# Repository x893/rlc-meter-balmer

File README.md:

# RLC-Meter-balmer
Complex impedance meter capable of measuring impedance in the range 1 mOhm - 10 MW at a frequency of 100 Hz to 250 kHz. Much attention is paid to measurement accuracy. Accuracy of better than 0.5% in the range 10 ohms - 100 ohms at frequencies of 100 Hz - 100 kHz.

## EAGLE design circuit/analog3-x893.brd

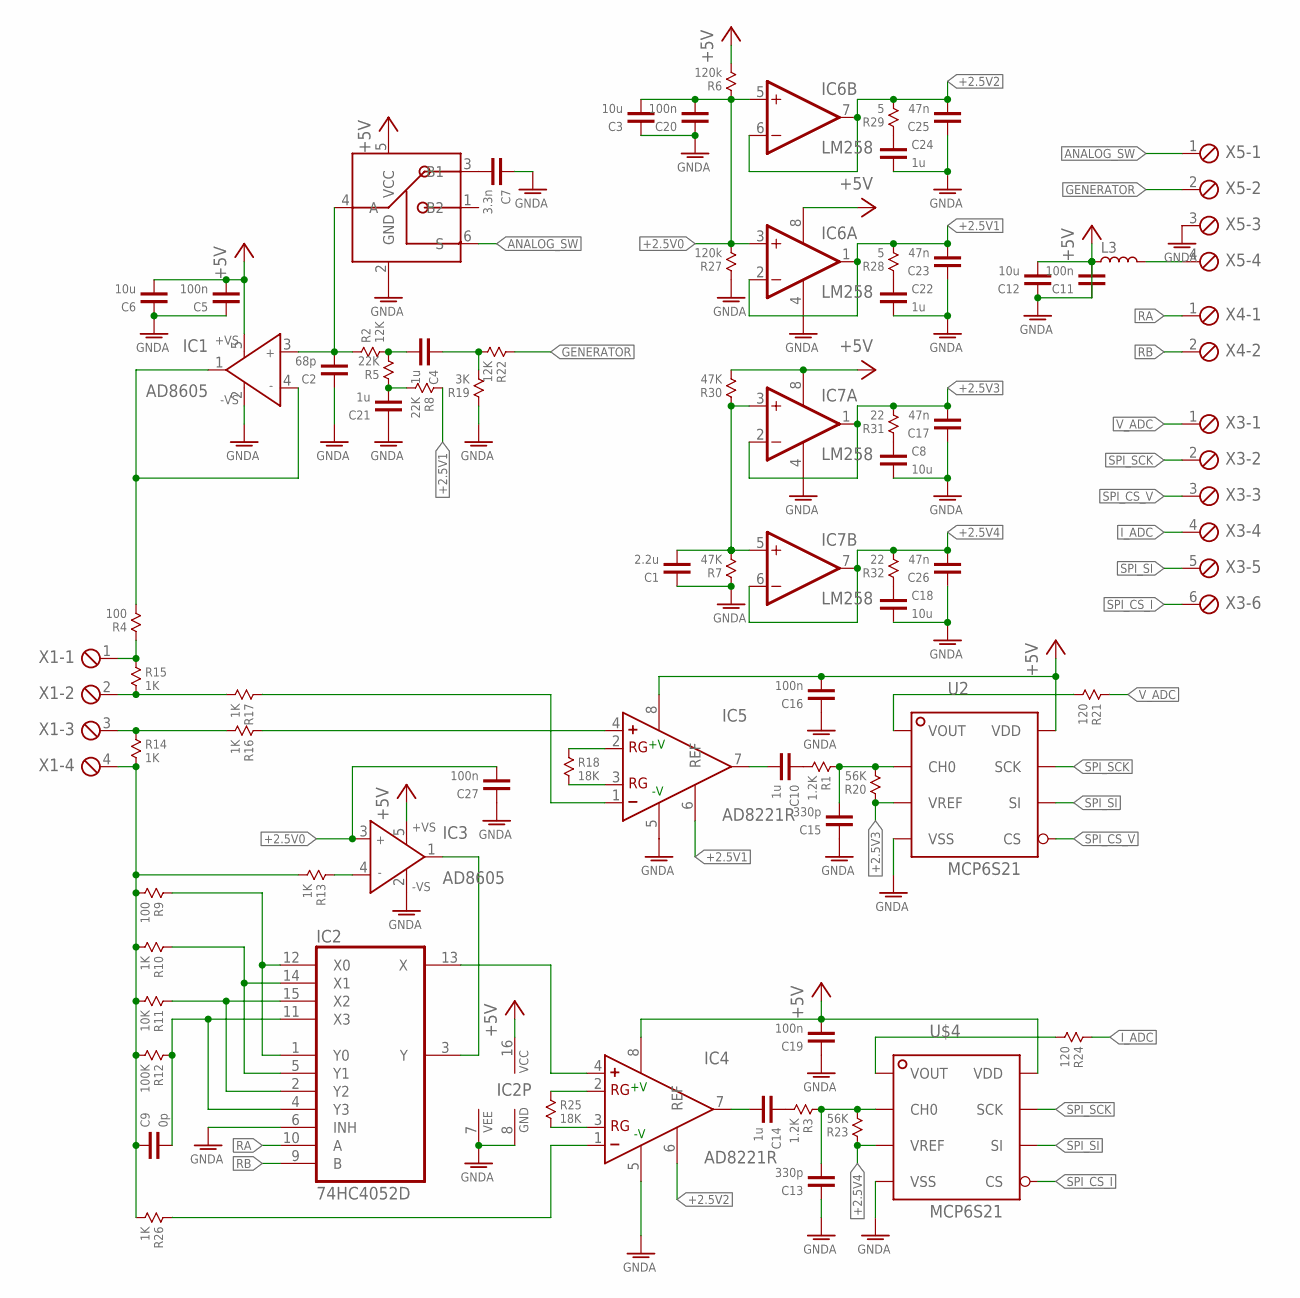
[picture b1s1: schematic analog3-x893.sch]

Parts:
C1: 2.2u; 0603
C2: 68p; 0603
C3, C6, C8, C12, C18: 10u; 0603
C4, C10, C14, C21, C22, C24: 1u; 0603
C5, C11, C16, C19, C20, C27: 100n; 0603
C7: 3.3n; 0603
C9: 0p; 0603
C13, C15: 330p; 0603
C17, C23, C25, C26: 47n; 0603
IC1, IC3: AD8605; SOT23-5
IC2: 74HC4052D; SO16
IC4, IC5: AD8221R; SO8
IC6, IC7: LM258; SO08
L3: INDUCTOR-0603; 0603
R1, R3: 1.2K; 0603
R2, R22: 12K; 0603
R4, R9: 100; 0603
R5, R8: 22K; 0603
R6, R27: 120k; 0603
R7, R30: 47K; 0603
R10, R13, R14, R15, R16, R17, R26: 1K; 0603
R11: 10K; 0603
R12: 100K; 0603
R18, R25: 18K; 0603
R19: 3K; 0603
R20, R23: 56K; 0603
R21, R24: 120; 0603
R28, R29: 5; 0603
R31, R32: 22; 0603
U2: MCP6S21; SO8
U$1: SN74LVC1G3157DBVR; SOT23-6
U$4: MCP6S21; SO8
X1, X5: MPT4; 4POL254
X3: MPT6; 6POL254
X4: MPT2; 2POL254

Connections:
+2.5V0: C3.1, C20.1, C27.1, IC3.3 (IN+), IC6.3 (+IN), IC6.5 (+IN), R6.1, R27.2
+2.5V1: C23.1, IC5.6 (REF), IC6.1 (OUT), IC6.2 (-IN), R8.1, R28.2
+2.5V2: C25.1, IC4.6 (REF), IC6.6 (-IN), IC6.7 (OUT), R29.2
+2.5V3: C17.1, IC7.1 (OUT), IC7.2 (-IN), R20.1, R31.2, U2.3 (VREF)
+2.5V4: C26.1, IC7.6 (-IN), IC7.7 (OUT), R23.1, R32.2, U$4.3 (VREF)
+5V: C5.1, C6.1, C11.1, C12.1, C16.1, C19.1, IC1.5 (+VS), IC2.16 (VCC), IC3.5 (+VS), IC4.8 (+V), IC5.8 (+V), IC6.8 (V+), IC7.8 (V+), L3.1, R6.2, R30.2, U2.8 (VDD), U$1.5 (VCC), U$4.8 (VDD)
ANALOG_SW: U$1.6 (S), X5.1
GENERATOR: R22.1, X5.2
GNDA: C1.2, C2.2, C3.2, C5.2, C6.2, C7.2, C8.1, C11.2, C12.2, C13.2, C15.2, C16.2, C17.2, C18.1, C19.2, C20.2, C21.2, C22.1, C23.2, C24.1, C25.2, C26.2, C27.2, IC1.2 (-VS), IC2.6 (INH), IC2.7 (VEE), IC2.8 (GND), IC3.2 (-VS), IC4.5 (-V), IC5.5 (-V), IC6.4 (V-), IC7.4 (V-), R7.1, R19.1, R27.1, U2.4 (VSS), U$1.2 (GND), U$4.4 (VSS), X5.3
I_ADC: R24.1, X3.4
unnamed: IC5.1 (-), R17.1
unnamed: C2.1, IC1.3 (IN+), R2.1, U$1.4 (A)
unnamed: C4.1, R2.2, R5.2
unnamed: IC1.1 (OUT), IC1.4 (IN-), R4.2
unnamed: L3.2, X5.4
unnamed: C7.1, U$1.3 (B1)
unnamed: IC3.4 (IN-), R13.1
unnamed: IC4.3 (RG), R25.2
unnamed: C21.1, R5.1, R8.2
unnamed: IC2.3 (Y), IC3.1 (OUT)
unnamed: IC2.1 (Y0), IC2.12 (X0), R9.1
unnamed: IC2.5 (Y1), IC2.14 (X1), R10.1
unnamed: IC2.2 (Y2), IC2.15 (X2), R11.1
unnamed: C9.1, IC2.4 (Y3), IC2.11 (X3), R12.1
unnamed: R14.1, R16.2, X1.3
unnamed: R15.2, R17.2, X1.2
unnamed: C9.2, R9.2, R10.2, R11.2, R12.2, R13.2, R14.2, R26.2, X1.4
unnamed: R4.1, R15.1, X1.1
unnamed: C10.1, IC5.7 (OUT)
unnamed: IC4.2 (RG), R25.1
unnamed: IC4.1 (-), R26.1
unnamed: IC5.3 (RG), R18.2
unnamed: IC5.2 (RG), R18.1
unnamed: C13.1, R3.1, R23.2, U$4.2 (CH0)
unnamed: R24.2, U$4.1 (VOUT)
unnamed: C15.1, R1.1, R20.2, U2.2 (CH0)
unnamed: R21.2, U2.1 (VOUT)
unnamed: C14.1, IC4.7 (OUT)
unnamed: IC2.13 (X), IC4.4 (+)
unnamed: C24.2, R29.1
unnamed: IC5.4 (+), R16.1
unnamed: C8.2, R31.1
unnamed: C4.2, R19.2, R22.2
unnamed: C18.2, R32.1
unnamed: C22.2, R28.1
unnamed: C10.2, R1.2
unnamed: C14.2, R3.2
unnamed: C1.1, IC7.3 (+IN), IC7.5 (+IN), R7.2, R30.1
RA: IC2.10 (A), X4.1
RB: IC2.9 (B), X4.2
SPI_CS_I: U$4.5 (CS), X3.6
SPI_CS_V: U2.5 (CS), X3.3
SPI_SCK: U2.7 (SCK), U$4.7 (SCK), X3.2
SPI_SI: U2.6 (SI), U$4.6 (SI), X3.5
V_ADC: R21.1, X3.1

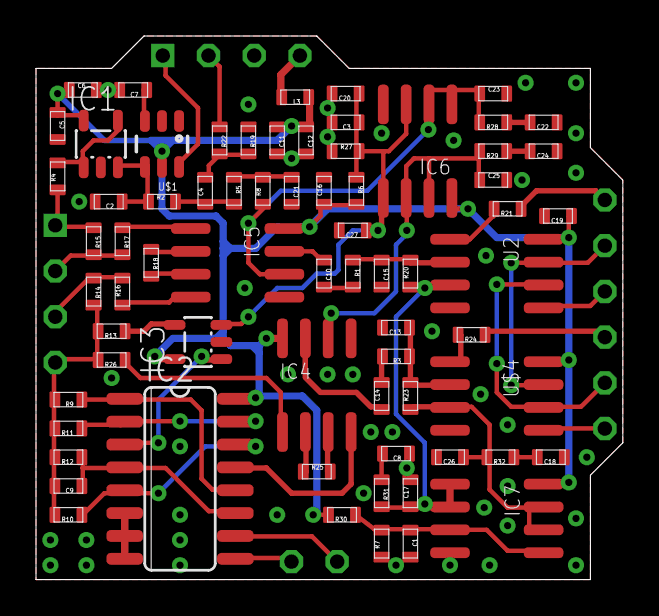
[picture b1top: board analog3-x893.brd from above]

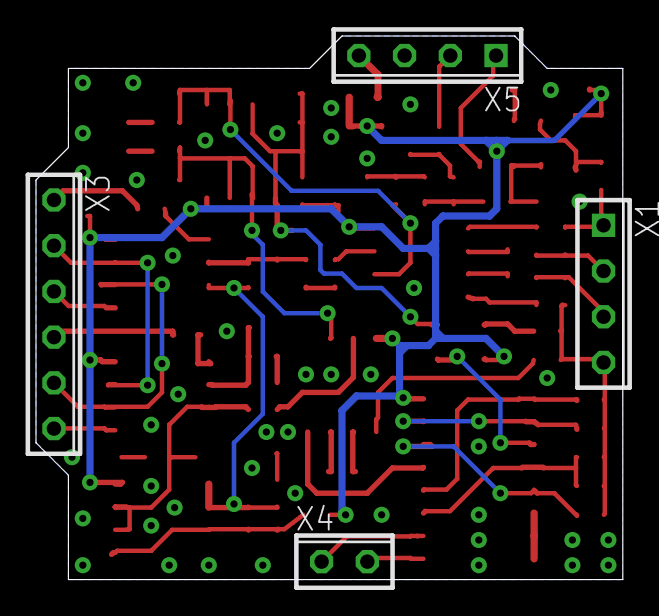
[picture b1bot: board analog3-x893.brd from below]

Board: 2 copper layers, 32.6 x 30.2 mm, 74 parts (4 on the bottom side), 55 nets.

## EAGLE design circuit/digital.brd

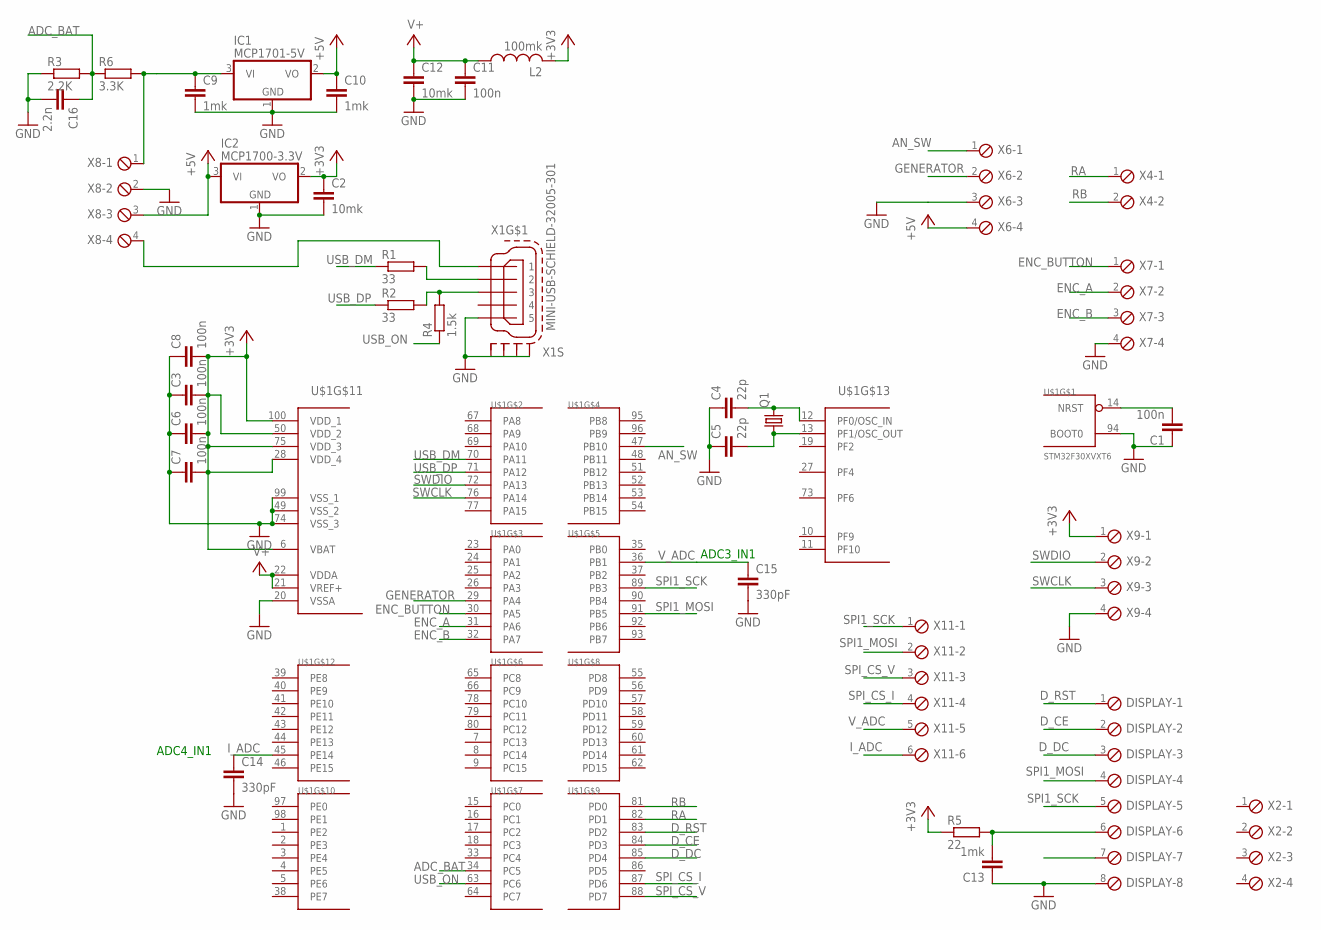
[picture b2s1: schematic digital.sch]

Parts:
C1, C3, C6, C7, C8, C11: 100n; C0603
C2, C12: 10mk; C0805
C4, C5: 22p; C0805
C9, C10, C13: 1mk; C0603
C14, C15: 330pF; C0805
C16: 2.2n; C0805
DISPLAY: MPT8; 8POL254
IC1: MCP1701-5V; SOT23
IC2: MCP1700-3.3V; SOT23
L2: 100mk; 0204/7
Q1: CRYSTALHC49UP; HC49UP
R1, R2: 33; R0603
R3: 2.2K; R0603
R4: 1.5k; R0603
R5: 22; R0603
R6: 3.3K; R0603
U$1: STM32F30XVXT6; TQFP100
X1: MINI-USB-SCHIELD-32005-301; 32005-301
X2, X6, X7, X8, X9: MPT4; 4POL254
X4: MPT2; 2POL254
X11: MPT6; 6POL254

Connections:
+3V3: C2.1, C3.2, C6.2, C7.2, C8.2, IC2.2 (VO), L2.2, R5.1, U$1.6 (VBAT), U$1.28 (VDD_4), U$1.50 (VDD_2), U$1.75 (VDD_3), U$1.100 (VDD_1), X9.1
+5V: C10.1, IC1.2 (VO), IC2.3 (VI), X6.4, X8.3
ADC_BAT: C16.1, R3.2, R6.1, U$1.34 (PC5)
AN_SW: U$1.47 (PB10), X6.1
D_CE: DISPLAY.2, U$1.84 (PD3)
D_DC: DISPLAY.3, U$1.85 (PD4)
D_RST: DISPLAY.1, U$1.83 (PD2)
ENC_A: U$1.31 (PA6), X7.2
ENC_B: U$1.32 (PA7), X7.3
ENC_BUTTON: U$1.30 (PA5), X7.1
GENERATOR: U$1.29 (PA4), X6.2
GND: C1.1, C2.2, C3.1, C4.1, C5.1, C6.1, C7.1, C8.1, C9.2, C10.2, C11.2, C12.2, C13.1, C14.2, C15.2, C16.2, DISPLAY.8, IC1.1 (GND), IC2.1 (GND), R3.1, U$1.20 (VSSA), U$1.49 (VSS_2), U$1.74 (VSS_3), U$1.94 (BOOT0), U$1.99 (VSS_1), X1.5, X1.M1 (S1), X1.M2 (S2), X1.M3 (S3), X1.M4 (S4), X6.3, X7.4, X8.2, X9.4
I_ADC: C14.1, U$1.45 (PE14), X11.6
unnamed: R1.2, X1.2
unnamed: R2.2, R4.2, X1.3
unnamed: C1.2, U$1.14 (NRST)
unnamed: C4.2, Q1.2, U$1.12 (PF0/OSC_IN)
unnamed: C5.2, Q1.1, U$1.13 (PF1/OSC_OUT)
unnamed: C13.2, DISPLAY.6, R5.2
unnamed: C9.1, IC1.3 (VI), R6.2, X8.1
unnamed: X1.1, X8.4
RA: U$1.82 (PD1), X4.1
RB: U$1.81 (PD0), X4.2
SPI1_MOSI: DISPLAY.4, U$1.91 (PB5), X11.2
SPI1_SCK: DISPLAY.5, U$1.89 (PB3), X11.1
SPI_CS_I: U$1.87 (PD6), X11.4
SPI_CS_V: U$1.88 (PD7), X11.3
SWCLK: U$1.76 (PA14), X9.3
SWDIO: U$1.72 (PA13), X9.2
USB_DM: R1.1, U$1.70 (PA11)
USB_DP: R2.1, U$1.71 (PA12)
USB_ON: R4.1, U$1.63 (PC6)
V+: C11.1, C12.1, L2.1, U$1.21 (VREF+), U$1.22 (VDDA)
V_ADC: C15.1, U$1.36 (PB1), X11.5

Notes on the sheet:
ADC4_IN1
ADC3_IN1

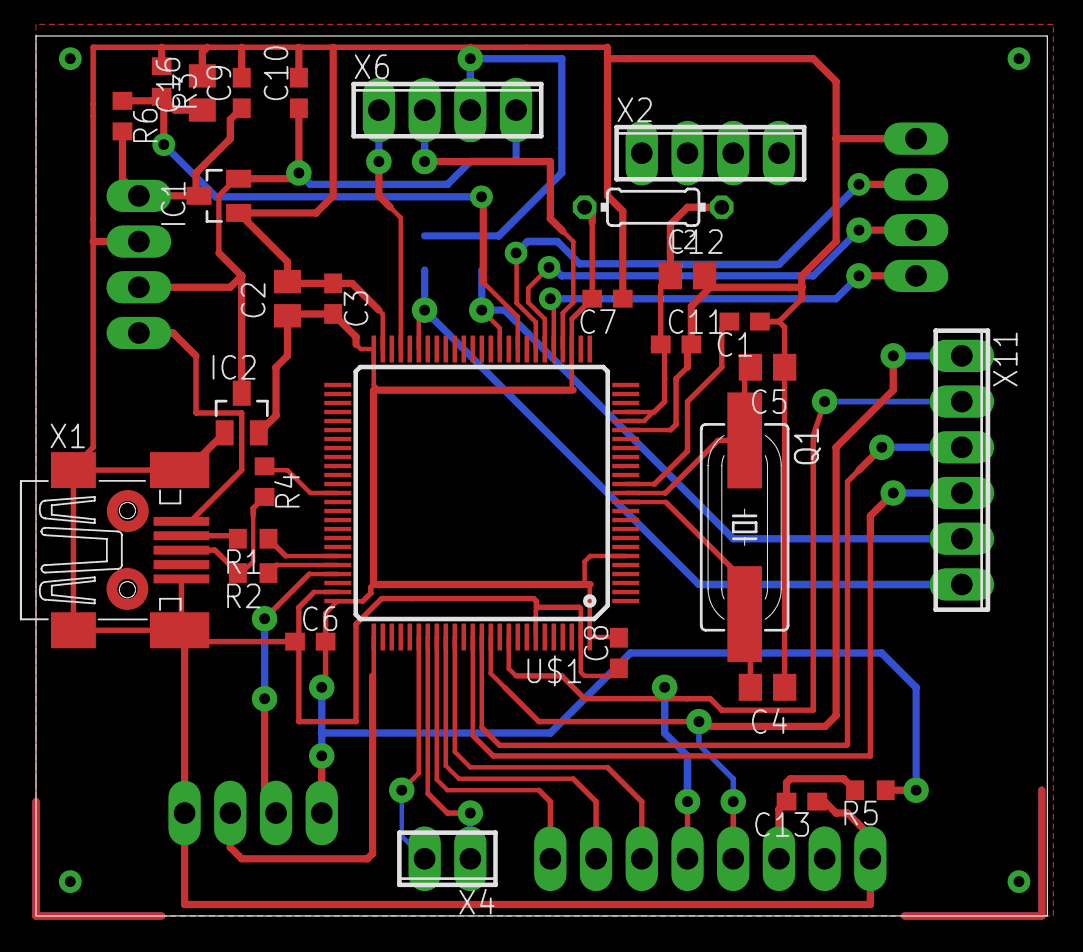
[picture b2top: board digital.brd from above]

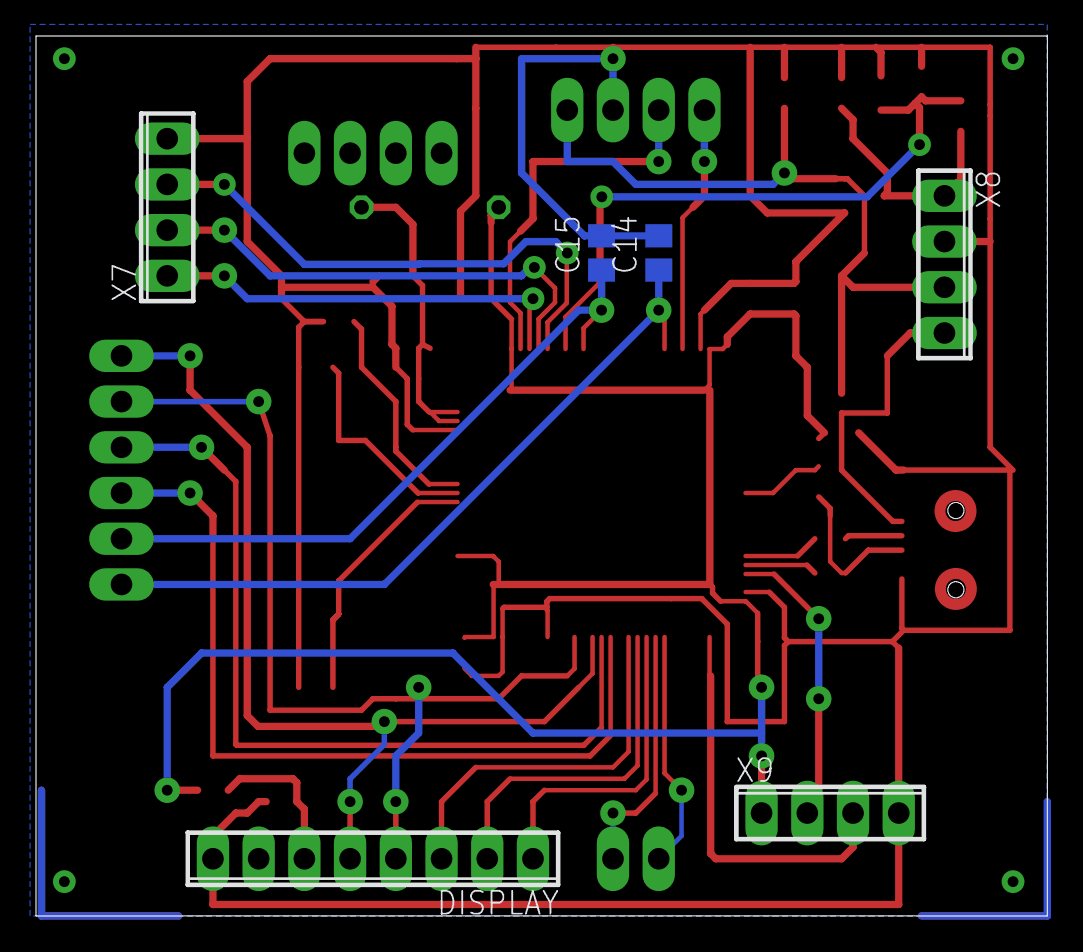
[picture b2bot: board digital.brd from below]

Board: 2 copper layers, 56.2 x 48.9 mm, 36 parts (6 on the bottom side), 34 nets.

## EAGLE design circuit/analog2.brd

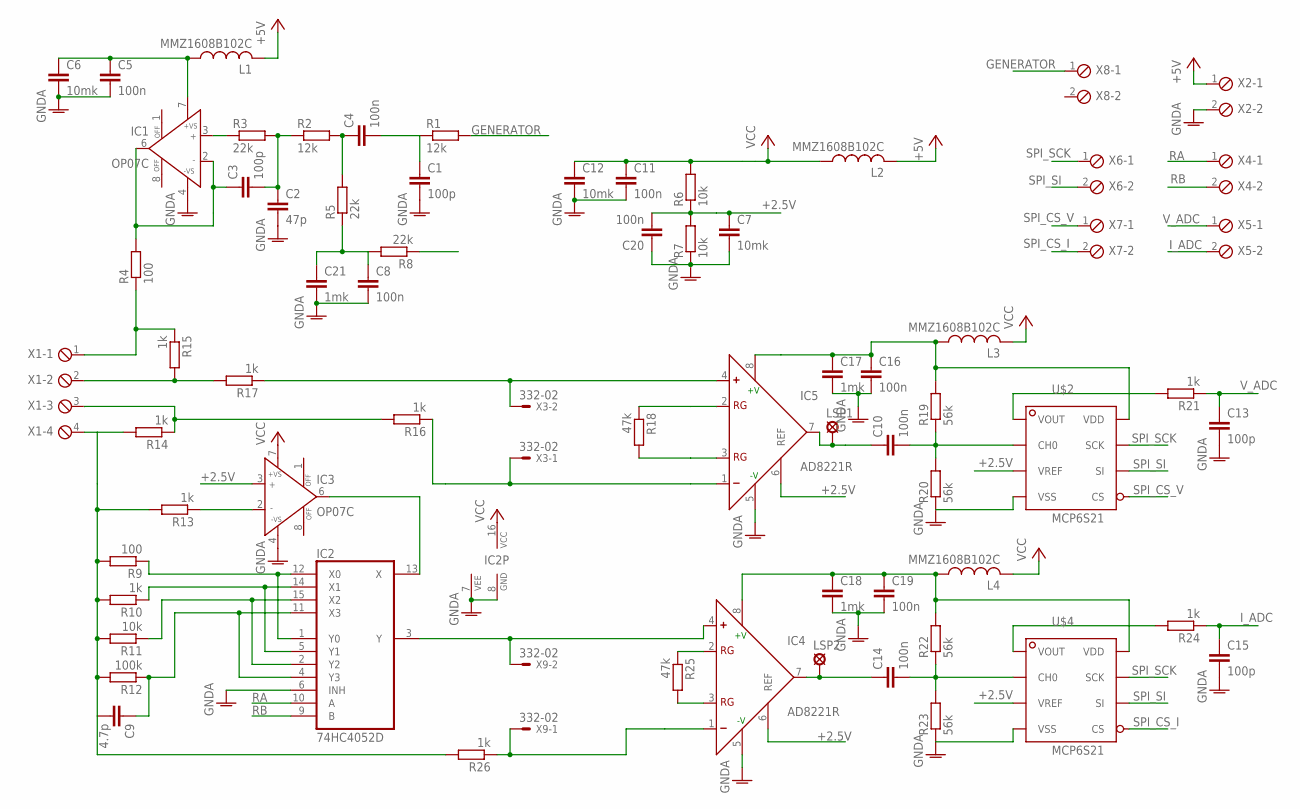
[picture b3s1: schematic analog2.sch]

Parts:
C1, C13, C15: 100p; C0805
C2: 47p; C0805
C3: 100p; C1206
C4, C5, C8, C10, C11, C14, C16, C19, C20: 100n; C0603
C6, C7, C12: 10mk; C0805
C9: 4.7p; C0805
C17, C18, C21: 1mk; C0603
IC1, IC3: OP07C; SO8
IC2: 74HC4052D; SO16
IC4, IC5: AD8221R; SO8
L1, L2, L3, L4: MMZ1608B102C; R0603
LSP1, LSP2: LSP10
R1, R2: 12k; R0805
R3, R5, R8: 22k; R0805
R4, R9: 100; R0805
R6, R7, R11: 10k; R0805
R10, R13, R14, R15, R16, R17, R21, R24, R26: 1k; R0805
R12: 100k; R0805
R18, R25: 47k; R0805
R19, R20, R22, R23: 56k; R0805
U$2, U$4: MCP6S21; SO8
X1: MPT4; 4POL254
X2, X4, X5, X6, X7, X8: MPT2; 2POL254
X3, X9: 332-02

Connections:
+2.5V: C7.1, C20.2, IC3.3 (IN+), IC4.6 (REF), IC5.6 (REF), R6.1, R7.2, R8.1, U$2.3 (VREF), U$4.3 (VREF)
+5V: L1.2, L2.2, X2.1
GENERATOR: R1.2, X8.1
GNDA: C1.2, C2.2, C5.2, C6.2, C7.2, C8.2, C11.2, C12.2, C13.2, C15.2, C16.2, C17.2, C18.2, C19.2, C20.1, C21.2, IC1.4 (-VS), IC2.6 (INH), IC2.7 (VEE), IC2.8 (GND), IC3.4 (-VS), IC4.5 (-V), IC5.5 (-V), R7.1, R20.1, R23.1, U$2.4 (VSS), U$4.4 (VSS), X2.2
I_ADC: C15.1, R24.1, X5.2
unnamed: IC5.4 (+), R17.1, X3.2
unnamed: C1.1, C4.2, R1.1
unnamed: C2.1, C3.2, R2.1, R3.2
unnamed: C4.1, R2.2, R5.2
unnamed: C3.1, IC1.2 (IN-), IC1.6 (OUT), R4.2
unnamed: IC1.3 (IN+), R3.1
unnamed: C5.1, C6.1, IC1.7 (+VS), L1.1
unnamed: IC3.2 (IN-), R13.1
unnamed: IC4.3 (RG), R25.2
unnamed: C8.1, C21.1, R5.1, R8.2
unnamed: IC2.13 (X), IC3.6 (OUT)
unnamed: IC2.1 (Y0), IC2.12 (X0), R9.1
unnamed: IC2.5 (Y1), IC2.14 (X1), R10.1
unnamed: IC2.2 (Y2), IC2.15 (X2), R11.1
unnamed: C9.1, IC2.4 (Y3), IC2.11 (X3), R12.1
unnamed: R14.1, R16.2, X1.3
unnamed: R15.2, R17.2, X1.2
unnamed: C9.2, R9.2, R10.2, R11.2, R12.2, R13.2, R14.2, R26.2, X1.4
unnamed: R4.1, R15.1, X1.1
unnamed: C10.1, IC5.7 (OUT), LSP1.MP
unnamed: IC4.2 (RG), R25.1
unnamed: IC4.1 (-), R26.1, X9.1
unnamed: IC5.3 (RG), R18.2
unnamed: IC5.2 (RG), R18.1
unnamed: C14.2, R22.1, R23.2, U$4.2 (CH0)
unnamed: R24.2, U$4.1 (VOUT)
unnamed: C10.2, R19.1, R20.2, U$2.2 (CH0)
unnamed: R21.2, U$2.1 (VOUT)
unnamed: C14.1, IC4.7 (OUT), LSP2.MP
unnamed: IC2.3 (Y), IC4.4 (+), X9.2
unnamed: C16.1, C17.1, IC5.8 (+V), L3.1, R19.2, U$2.8 (VDD)
unnamed: C18.1, C19.1, IC4.8 (+V), L4.1, R22.2, U$4.8 (VDD)
RA: IC2.10 (A), X4.1
RB: IC2.9 (B), X4.2
SPI_CS_I: U$4.5 (CS), X7.2
SPI_CS_V: U$2.5 (CS), X7.1
SPI_SCK: U$2.7 (SCK), U$4.7 (SCK), X6.1
SPI_SI: U$2.6 (SI), U$4.6 (SI), X6.2
VCC: C11.1, C12.1, IC2.16 (VCC), IC3.7 (+VS), L2.1, L3.2, L4.2, R6.2
V_ADC: C13.1, R21.1, X5.1
V_IN+: IC5.1 (-), R16.1, X3.1

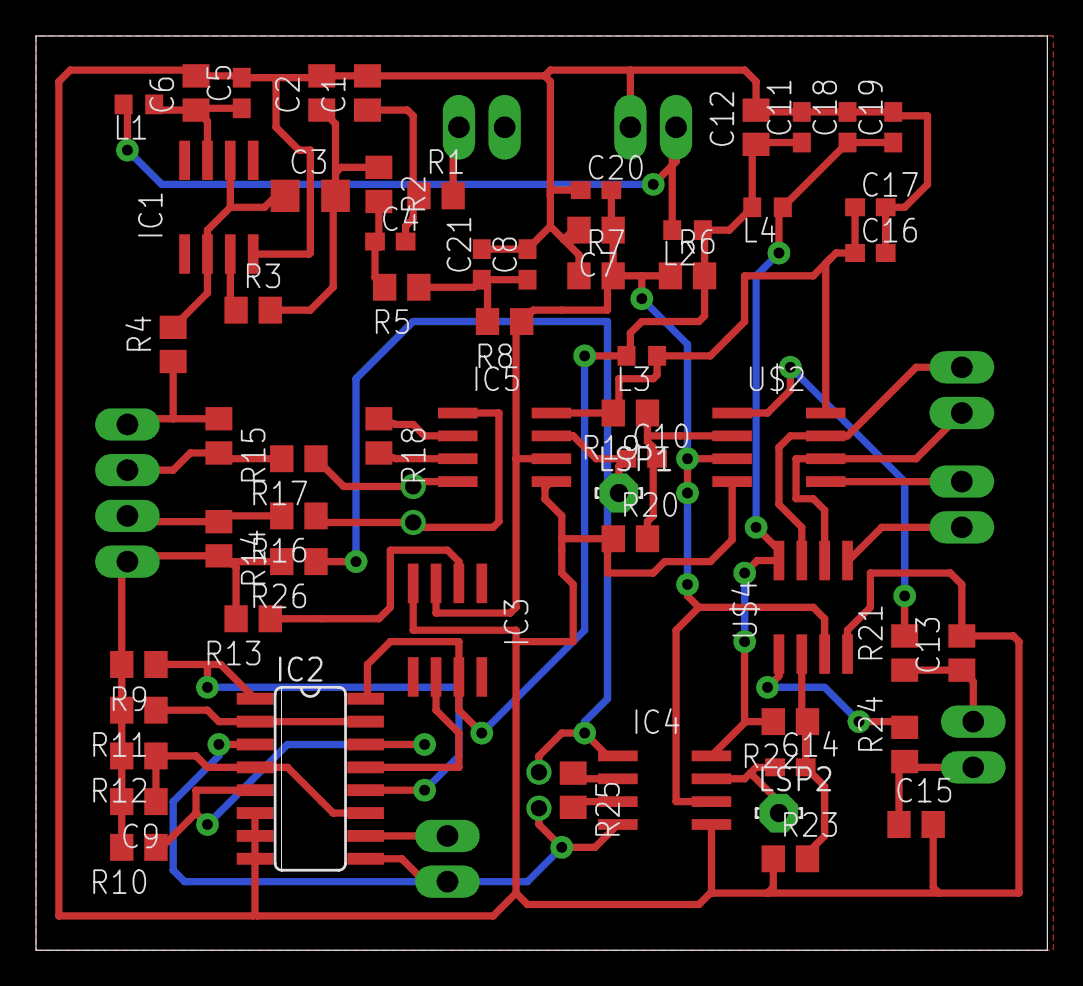
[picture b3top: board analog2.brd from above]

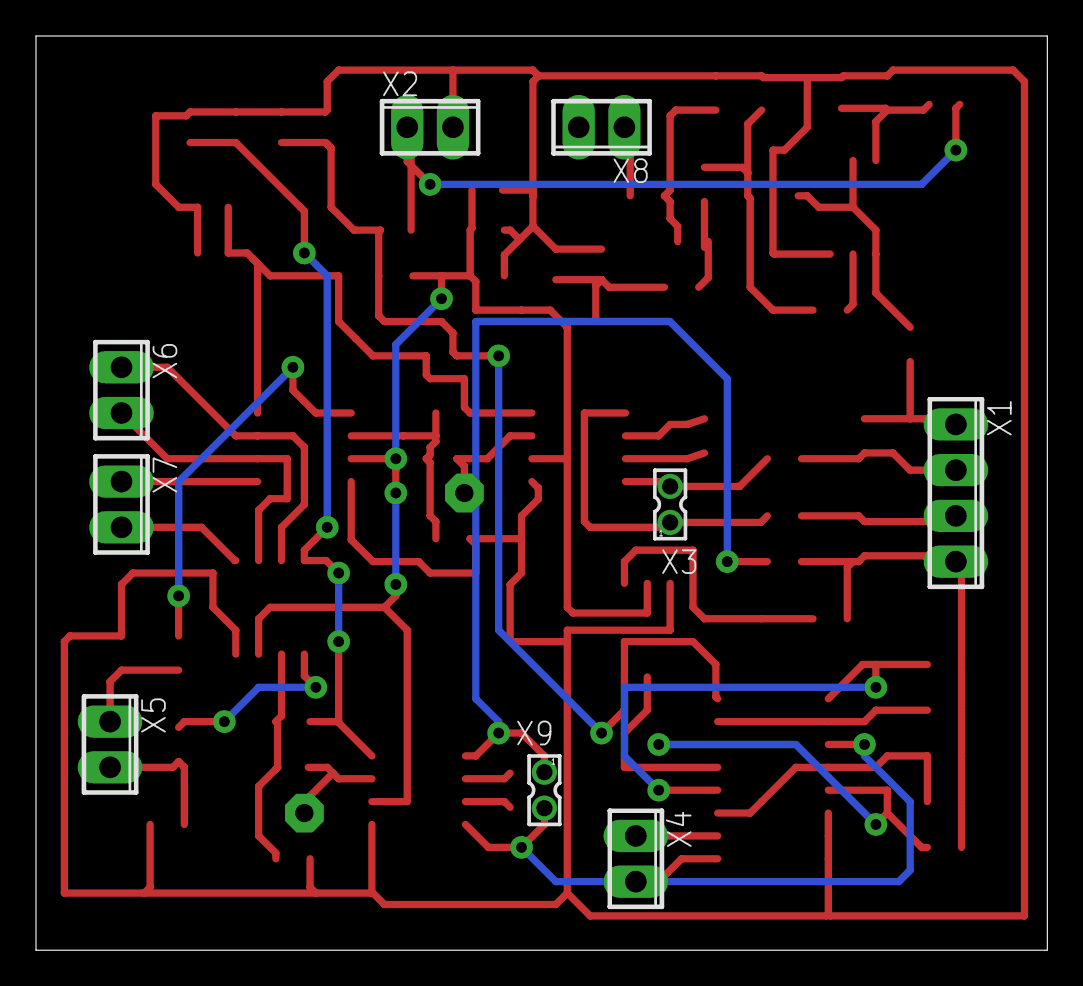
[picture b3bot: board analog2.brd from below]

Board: 2 copper layers, 56.2 x 50.8 mm, 69 parts (9 on the bottom side), 46 nets.

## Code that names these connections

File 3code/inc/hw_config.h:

// balmer@inbox.ru RLC Meter 303
// 2013-2014

#ifndef __HW_CONFIG_H
#define __HW_CONFIG_H

#include <stdbool.h>
#include <stdint.h>
#include "usb_type.h"

#if defined( STM32F30X ) || defined( STM32F303xC )
	#include "stm32f30x.h"
#endif /* STM32F30X */

#define NELEMENTS(a)		(sizeof(a) / sizeof(*(a)))
#define VIRTUAL_COM_PORT_DATA_SIZE	64

void Set_System				(void);
void Set_USBClock			(void);
void GPIO_AINConfig			(void);
void Enter_LowPowerMode		(void);
void Leave_LowPowerMode		(void);
void USB_Interrupts_Config	(void);
void USB_Cable_Config		(FunctionalState NewState);
void Get_SerialNum			(void);

#define USB_ON_PORT			GPIOC
#define USB_ON_PIN			GPIO_Pin_6
#define USB_INT_DEFAULT		// For Default Interrupt Mode
//	#define USB_INT_REMAP	// For Remapping Interrupt Mode

#define RCC_AHBPeriph_ALLGPIO	(RCC_AHBPeriph_GPIOA	\
								| RCC_AHBPeriph_GPIOB	\
								| RCC_AHBPeriph_GPIOC	\
								| RCC_AHBPeriph_GPIOD	\
								| RCC_AHBPeriph_GPIOE	\
								| RCC_AHBPeriph_GPIOF	\
								)

#define AN_SW_PORT			GPIOB
#define AN_SW_PIN			GPIO_Pin_10

#define RAB_PORT			GPIOD
#define RA_PIN				GPIO_Pin_1
#define RB_PIN				GPIO_Pin_0

#define LCD_BL_PORT			GPIOE
#define LCD_BL_PIN			GPIO_Pin_1
#define LCD_BL_RCC			RCC_AHBPeriph_GPIOE

#define LCD_RST_PORT		GPIOD
#define LCD_RST_PIN			GPIO_Pin_2

#define LCD_DC_PORT			GPIOD
#define LCD_DC_PIN			GPIO_Pin_4

#define LCD_CE_PORT			GPIOD
#define LCD_CE_PIN			GPIO_Pin_3

#define ADC_BAT_PORT		GPIOC
#define ADC_BAT_PIN			GPIO_Pin_5
#define ADC_BAT_RCC			RCC_AHBPeriph_GPIOC
#define ADC_BAT				ADC2
#define ADC_BAT_HIGH		3080	//6.2 V
#define ADC_BAT_LOW			2730	//5.5 V

#define V_ADC_PORT			GPIOB
#define V_ADC_PIN			GPIO_Pin_1
#define V_ADC_RCC			RCC_AHBPeriph_GPIOB

#define I_ADC_PORT			GPIOE
#define I_ADC_PIN			GPIO_Pin_14
#define I_ADC_RCC			RCC_AHBPeriph_GPIOE

#define GENERATOR_PORT		GPIOA
#define GENERATOR_PIN		GPIO_Pin_4
#define GENERATOR_PIN_CLK	RCC_AHBPeriph_GPIOA
#define GENERATOR_TIMER		TIM2
#define GENERATOR_TIMER_CLK	RCC_APB1Periph_TIM2

#define SPI1_PORT			GPIOB
#define SPI1_RCC			RCC_AHBPeriph_GPIOB
#define SPI1_MOSI_PIN		GPIO_Pin_5
#define SPI1_CLK_PIN		GPIO_Pin_3

#define SPI_CS_PORT			GPIOD
#define SPI_CS_RCC			RCC_AHBPeriph_GPIOD
#define SPI_CS_I_PIN		GPIO_Pin_6
#define SPI_CS_V_PIN		GPIO_Pin_7

#define DEF_INTERFACE_BUTTONS

#define Codeur_A			GPIO_Pin_6
#define Codeur_A_SOURCE		GPIO_PinSource6
#define Codeur_B			GPIO_Pin_7
#define Codeur_B_SOURCE		GPIO_PinSource7
#define Codeur_GPIO			GPIOA
#define Codeur_RCC			RCC_AHBPeriph_GPIOA
#define Codeur_AF			GPIO_AF_2
 
#define Codeur_TIMER		TIM3
#define Codeur_TIMER_RCC	RCC_APB1Periph_TIM3

#define BUTTON_PIN 			GPIO_Pin_5
#define BUTTON_GPIO			GPIOA

/*
  bit 0 = RA
  bit 1 = RB
*/
void SetResistor(uint8_t idx);

// 24000 == 3 KHz
#define LOW_PASS_PERIOD 24000
/*
Add 3.3 nF capacitor to filter after DAC.
*/
void SetLowPassFilter(bool on);

#endif  /*__HW_CONFIG_H*/

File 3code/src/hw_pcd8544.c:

// balmer@inbox.ru RLC Meter 303
// 2013-2014

#include "pcd8544.h"
#include "hw_config.h"
#include "hw_pcd8544.h"
#include "systick.h"

#define HARDWARE_SPI

//  SPI1
//	PB3 = SCK
//	PB5 = MOSI
//	PD2 = RST
//	PD3 = CE
//	PD4 = DC
void HwLcdInit()
{
	GPIO_InitTypeDef GPIO_InitStruct;
	SPI_InitTypeDef SPI_InitStruct;

	// enable clock for used IO pins
	RCC_AHBPeriphClockCmd(RCC_AHBPeriph_GPIOD, ENABLE);

	// configure RST, CE, DC
	GPIO_InitStruct.GPIO_Pin = LCD_DC_PIN | LCD_CE_PIN | LCD_RST_PIN;
	GPIO_InitStruct.GPIO_Mode = GPIO_Mode_OUT;
	GPIO_InitStruct.GPIO_OType = GPIO_OType_PP;
	GPIO_InitStruct.GPIO_Speed = GPIO_Speed_50MHz;
	GPIO_InitStruct.GPIO_PuPd = GPIO_PuPd_UP;
	GPIO_Init(LCD_DC_PORT, &GPIO_InitStruct);

#ifdef HARDWARE_SPI
	// enable clock for used IO pins
	RCC_AHBPeriphClockCmd(SPI1_RCC, ENABLE);

	// configure pins used by SPI
	GPIO_InitStruct.GPIO_Pin = SPI1_CLK_PIN | SPI1_MOSI_PIN;
	GPIO_InitStruct.GPIO_Mode = GPIO_Mode_AF;
	GPIO_InitStruct.GPIO_OType = GPIO_OType_PP;
	GPIO_InitStruct.GPIO_Speed = GPIO_Speed_50MHz;
	GPIO_InitStruct.GPIO_PuPd = GPIO_PuPd_NOPULL;
	GPIO_Init(SPI1_PORT, &GPIO_InitStruct);

	// connect SPI1 pins to SPI alternate function
	GPIO_PinAFConfig(SPI1_PORT, SPI1_CLK_PIN, GPIO_AF_5);
	GPIO_PinAFConfig(SPI1_PORT, SPI1_MOSI_PIN, GPIO_AF_5);

	// enable peripheral clock
	RCC_APB2PeriphClockCmd(RCC_APB2Periph_SPI1, ENABLE);

	// configure SPI1 in Mode 0 
	// CPOL = 0 --> clock is low when idle
	// CPHA = 0 --> data is sampled at the first edge
	SPI_InitStruct.SPI_Direction = SPI_Direction_1Line_Tx;
	SPI_InitStruct.SPI_Mode = SPI_Mode_Master;
	SPI_InitStruct.SPI_DataSize = SPI_DataSize_16b;
	SPI_InitStruct.SPI_CPOL = SPI_CPOL_Low;
	SPI_InitStruct.SPI_CPHA = SPI_CPHA_1Edge;
	SPI_InitStruct.SPI_NSS = SPI_NSS_Soft | SPI_NSSInternalSoft_Set;
	SPI_InitStruct.SPI_BaudRatePrescaler = SPI_BaudRatePrescaler_32;
	SPI_InitStruct.SPI_FirstBit = SPI_FirstBit_MSB;
	SPI_Init(SPI1, &SPI_InitStruct);

	SPI_Cmd(SPI1, ENABLE);

#else

	RCC_AHBPeriphClockCmd(SPI1_RCC, ENABLE);

	// configure pins used by SPI1
	GPIO_InitStruct.GPIO_Pin = SPI1_CLK_PIN | SPI1_MOSI_PIN;
	GPIO_InitStruct.GPIO_Mode = GPIO_Mode_OUT;
	GPIO_InitStruct.GPIO_OType = GPIO_OType_PP;
	GPIO_InitStruct.GPIO_Speed = GPIO_Speed_50MHz;
	GPIO_InitStruct.GPIO_PuPd = GPIO_PuPd_NOPULL;
	GPIO_Init(SPI1_PORT, &GPIO_InitStruct);

	GPIO_WriteBit(SPI1_PORT, SPI1_CLK_PIN, 1);
#endif
}

void DelaySome()
{
	delay_ms(50);
}

void HwLcdPinCE(uint8_t on)
{
	GPIO_WriteBit(LCD_CE_PORT, LCD_CE_PIN, (BitAction)on);
}

void HwLcdPinDC(uint8_t on)
{
	GPIO_WriteBit(LCD_DC_PORT, LCD_DC_PIN, (BitAction)on);
}

void HwLcdPinRst(uint8_t on)
{
	GPIO_WriteBit(LCD_RST_PORT, LCD_RST_PIN, (BitAction)on);
}

void HwLcdSend(uint16_t data)
{
#ifdef HARDWARE_SPI

	SPI1->DR = data;
	while (!(SPI1->SR & SPI_I2S_FLAG_TXE))
		;	// wait until transmit complete
	while (SPI1->SR & SPI_I2S_FLAG_BSY)
		;	// wait until SPI is not busy anymore

#else

	unsigned char i;
	for (i = 0; i < 16; i++)
	{
		for (volatile int j = 0; j < 4; j++)
			;
		GPIO_WriteBit(SPI1_PORT, SPI1_MOSI_PIN, (data & 0x8000) ? 1 : 0);
		data = data << 1;

		for (volatile int j = 0; j < 32; j++)
			;
		GPIO_WriteBit(SPI1_PORT, SPI1_CLK_PIN, 0);

		for (volatile int j = 0; j < 32; j++)
			;
		GPIO_WriteBit(SPI1_PORT, SPI1_CLK_PIN, 1);
	}

#endif
}

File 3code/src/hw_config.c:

// balmer@inbox.ru RLC Meter 303
// 2013-2014

#include "main.h"

ErrorStatus HSEStartUpStatus;
EXTI_InitTypeDef EXTI_InitStructure;

/* Private function prototypes -----------------------------------------------*/
static void IntToUnicode(uint32_t value, uint8_t *pbuf, uint8_t len);
/* Private functions ---------------------------------------------------------*/

/**
  * @brief  Configures Main system clocks & power.
  * @param  None
  * @retval None
  */
void Set_System(void)
{
	GPIO_InitTypeDef  GPIO_InitStructure;

	/*!< At this stage the microcontroller clock setting is already configured,
		 this is done through SystemInit() function which is called from startup
		 file (startup_stm32f30x.s) before to branch to application main.
		 To reconfigure the default setting of SystemInit() function, refer to
		 system_stm32f30x.c file
		 */

	// Enable the PWR clock
	RCC_APB1PeriphClockCmd(RCC_APB1Periph_PWR, ENABLE);

	// Enable the SYSCFG module clock (used for the USB disconnect feature)
	RCC_APB2PeriphClockCmd(RCC_APB2Periph_SYSCFG, ENABLE);

	// Set PA11,12 as IN - USB_DM,DP
	RCC_AHBPeriphClockCmd(RCC_AHBPeriph_GPIOA, ENABLE);
	GPIO_InitStructure.GPIO_Pin = GPIO_Pin_11 | GPIO_Pin_12;
	GPIO_InitStructure.GPIO_Speed = GPIO_Speed_50MHz;
	GPIO_InitStructure.GPIO_Mode = GPIO_Mode_AF;
	GPIO_InitStructure.GPIO_OType = GPIO_OType_PP;
	GPIO_InitStructure.GPIO_PuPd = GPIO_PuPd_NOPULL;
	GPIO_Init(GPIOA, &GPIO_InitStructure);

	// SET PA11,12 for USB: USB_DM,DP
	GPIO_PinAFConfig(GPIOA, GPIO_PinSource11, GPIO_AF_14);
	GPIO_PinAFConfig(GPIOA, GPIO_PinSource12, GPIO_AF_14);

	// PC6 used as USB pull-up
	// Enable the USB disconnect GPIO clock
	RCC_AHBPeriphClockCmd(RCC_AHBPeriph_GPIOC, ENABLE);

	// USB_ON_PORT used as USB pull-up
	GPIO_InitStructure.GPIO_Pin = USB_ON_PIN;
	GPIO_InitStructure.GPIO_Mode = GPIO_Mode_OUT;
	GPIO_InitStructure.GPIO_Speed = GPIO_Speed_2MHz;
	GPIO_InitStructure.GPIO_OType = GPIO_OType_PP;
	GPIO_InitStructure.GPIO_PuPd = GPIO_PuPd_NOPULL;
	GPIO_Init(USB_ON_PORT, &GPIO_InitStructure);

	// Configure the EXTI line 18 connected internally to the USB IP
	EXTI_ClearITPendingBit(EXTI_Line18);
	EXTI_InitStructure.EXTI_Line = EXTI_Line18; /* USB resume from suspend mode */
	EXTI_InitStructure.EXTI_Mode = EXTI_Mode_Interrupt;
	EXTI_InitStructure.EXTI_Trigger = EXTI_Trigger_Rising;
	EXTI_InitStructure.EXTI_LineCmd = ENABLE;
	EXTI_Init(&EXTI_InitStructure);

	// Set resistor pins (RA, RB)
	RCC_AHBPeriphClockCmd(RCC_AHBPeriph_GPIOD, ENABLE);
	GPIO_InitStructure.GPIO_Pin = RA_PIN | RB_PIN;
	GPIO_InitStructure.GPIO_Mode = GPIO_Mode_OUT;
	GPIO_InitStructure.GPIO_Speed = GPIO_Speed_2MHz;
	GPIO_InitStructure.GPIO_OType = GPIO_OType_PP;
	GPIO_InitStructure.GPIO_PuPd = GPIO_PuPd_NOPULL;
	GPIO_Init(RAB_PORT, &GPIO_InitStructure);

	SetResistor(0);

	// Set Analog Switch pin
	RCC_AHBPeriphClockCmd(RCC_AHBPeriph_GPIOB, ENABLE);
	GPIO_InitStructure.GPIO_Pin = AN_SW_PIN;
	GPIO_InitStructure.GPIO_Mode = GPIO_Mode_OUT;
	GPIO_InitStructure.GPIO_Speed = GPIO_Speed_2MHz;
	GPIO_InitStructure.GPIO_OType = GPIO_OType_PP;
	GPIO_InitStructure.GPIO_PuPd = GPIO_PuPd_NOPULL;
	GPIO_Init(AN_SW_PORT, &GPIO_InitStructure);

	SetLowPassFilter(false);
}

/**
  * @brief  Configures USB Clock input (48MHz).
  * @param  None
  * @retval None
  */
void Set_USBClock(void)
{
	/* USBCLK = PLLCLK = 48 MHz */
	RCC_USBCLKConfig(RCC_USBCLKSource_PLLCLK_1Div5);

	/* Enable USB clock */
	RCC_APB1PeriphClockCmd(RCC_APB1Periph_USB, ENABLE);
}

/**
  * @brief  Configures all IOs as AIN to reduce the power consumption.
  * @param  None
  * @retval None
  */
void GPIO_AINConfig(void)
{
	GPIO_InitTypeDef GPIO_InitStructure;

	/* Configure all GPIO port pins in Analog Input mode (floating input trigger OFF) */

	/* Enable all GPIOs Clock */
	RCC_AHBPeriphClockCmd(RCC_AHBPeriph_ALLGPIO, ENABLE);

	/* Configure all GPIO port pins in Analog Input mode (floating input trigger OFF) */

	GPIO_InitStructure.GPIO_Pin = GPIO_Pin_All;
	GPIO_InitStructure.GPIO_Mode = GPIO_Mode_AN;
	GPIO_Init(GPIOC, &GPIO_InitStructure);
	GPIO_Init(GPIOD, &GPIO_InitStructure);
	GPIO_Init(GPIOE, &GPIO_InitStructure);

	/* Disable all GPIOs Clock */
	RCC_AHBPeriphClockCmd(RCC_AHBPeriph_ALLGPIO, DISABLE);
}

/**
  * @brief  Power-off system clocks and power while entering suspend mode.
  * @param  None
  * @retval None
  */
void Enter_LowPowerMode(void)
{
	/* Set the device state to suspend */
	bDeviceState = SUSPENDED;
}

/**
  * @brief  Restores system clocks and power while exiting suspend mode.
  * @param  None
  * @retval None
  */
void Leave_LowPowerMode(void)
{
	DEVICE_INFO *pInfo = &Device_Info;

	/* Enable HSE */
	RCC_HSEConfig(RCC_HSE_ON);

	/* Wait till HSE is ready */
	HSEStartUpStatus = RCC_WaitForHSEStartUp();

	/* Wait till HSE is ready */
	while (RCC_GetFlagStatus(RCC_FLAG_HSERDY) == RESET)
	{
	}

	/* Enable PLL1 */
	RCC_PLLCmd(ENABLE);

	/* Wait till PLL1 is ready */
	while (RCC_GetFlagStatus(RCC_FLAG_PLLRDY) == RESET)
	{
	}

	/* Select PLL as system clock source */
	RCC_SYSCLKConfig(RCC_SYSCLKSource_PLLCLK);

	/* Wait till PLL is used as system clock source */
	while (RCC_GetSYSCLKSource() != 0x08)
	{
	}

	/* Set the device state to the correct state */
	if (pInfo->Current_Configuration != 0)
	{
		/* Device configured */
		bDeviceState = CONFIGURED;
	}
	else
	{
		bDeviceState = ATTACHED;
	}
}

/**
  * @brief  Configures the USB interrupts.
  * @param  None
  * @retval None
  */
void USB_Interrupts_Config(void)
{
	NVIC_InitTypeDef NVIC_InitStructure;

	/* 2 bit for pre-emption priority, 2 bits for subpriority */
	NVIC_PriorityGroupConfig(NVIC_PriorityGroup_2);

	/* Enable the USB interrupt */
#if defined (USB_INT_DEFAULT)
	NVIC_InitStructure.NVIC_IRQChannel = USB_LP_CAN1_RX0_IRQn;
#endif
#if defined (USB_INT_REMAP)
	NVIC_InitStructure.NVIC_IRQChannel = USB_LP_IRQn;
#endif 
	NVIC_InitStructure.NVIC_IRQChannelPreemptionPriority = 2;
	NVIC_InitStructure.NVIC_IRQChannelSubPriority = 0;
	NVIC_InitStructure.NVIC_IRQChannelCmd = ENABLE;
	NVIC_Init(&NVIC_InitStructure);

	/* Enable the USB Wake-up interrupt */
#if defined (USB_INT_DEFAULT)
	NVIC_InitStructure.NVIC_IRQChannel = USBWakeUp_IRQn;
#endif

#if defined (USB_INT_REMAP)  
	NVIC_InitStructure.NVIC_IRQChannel = USBWakeUp_RMP_IRQn;
#endif  
	NVIC_InitStructure.NVIC_IRQChannelPreemptionPriority = 1;
	NVIC_InitStructure.NVIC_IRQChannelCmd = ENABLE;
	NVIC_Init(&NVIC_InitStructure);
}

/**
  * @brief  Software Connection/Disconnection of USB Cable.
  * @param  None
  * @retval None
  */
void USB_Cable_Config(FunctionalState NewState)
{
	if (NewState != DISABLE)
		GPIO_SetBits(USB_ON_PORT, USB_ON_PIN);
	else
		GPIO_ResetBits(USB_ON_PORT, USB_ON_PIN);
}


/**
  * @brief  Create the serial number string descriptor.
  * @param  None.
  * @retval None
  */
void Get_SerialNum(void)
{
	uint32_t Device_Serial0, Device_Serial1, Device_Serial2;

	Device_Serial0 = *(__IO uint32_t*)(0x1FFFF7E8);
	Device_Serial1 = *(__IO uint32_t*)(0x1FFFF7EC);
	Device_Serial2 = *(__IO uint32_t*)(0x1FFFF7F0);

	Device_Serial0 += Device_Serial2;

	if (Device_Serial0 != 0)
	{
		IntToUnicode(Device_Serial0, &RLC_StringSerial[2], 8);
		IntToUnicode(Device_Serial1, &RLC_StringSerial[18], 4);
	}
}

/**
  * @brief  Convert Hex 32Bits value into char.
  * @param  value: Data to be converted.
  * @param  pbuf: pointer to buffer.
  * @param  len: Data length.
  * @retval None
  */
static void IntToUnicode(uint32_t value, uint8_t *pbuf, uint8_t len)
{
	uint8_t idx = 0;
	uint8_t ch;

	while (len != 0)
	{
		--len;
		ch = (value >> 28);
		if (ch < 10)
			pbuf[idx] = ch + '0';
		else
			pbuf[idx] = ch + ('A' - 10);

		value <<= 4;
		pbuf[idx + 1] = 0;
		idx += 2;
	}
}

void SetResistor(uint8_t idx)
{
	GPIO_WriteBit(RAB_PORT, RA_PIN, (BitAction)((idx >> 0) & 1));
	GPIO_WriteBit(RAB_PORT, RB_PIN, (BitAction)((idx >> 1) & 1));
}

void SetLowPassFilter(bool on)
{
	GPIO_WriteBit(AN_SW_PORT, AN_SW_PIN, (on ? Bit_RESET : Bit_SET));
}

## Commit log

2013-10-27 - analog to dual ADC STM32F103
2013-10-27 - ????? ????????? ?????????????? ??? ?????? ????????? , AD8532 ????? ??????? ???????? Input offset voltage.
2013-10-27 - AD825, OP07C ?????????? ??? ?????????
2013-10-29 - SO8
2013-10-31 - ????????? ??? ???????????? ??? F103 ??????????
2013-11-03 - DAC 100 khz STM32F107
2013-11-04 - ????????? delay_us, delay_ms ????? ????????? ????? ??????
2013-11-05 - systick ?????? ??????? ?????, ?? ??????????? ? USB, ?? ???????? ?? 200 ms - ???????? USB ?? STM32F107 - ??????????????? ??????
2013-11-07 - ????????? ADC ?? ???????
2013-11-09 - ????????? ????????????????? ADC ? DAC
2013-11-10 - ????????? ???????? ???????? 600 ???? - 100 ???
2013-11-11 - dual mode
2013-11-19 - ?????? ??????? ???????? ??? ??? LM258 ? ???????? ???????? ??????????
2013-11-19 - ?????? ???? Unrouted
2013-11-24 - ??? ????? LCD ???????
2013-11-24 - ?????? 4 IO ???? ?? ???? ??????, ??? LCD
2013-11-24 - ???? ??????? ??? USB
2013-11-27 - 0.25 ?? ?????? ? STM32
2013-12-10 - ???????? ?? USB
2013-12-10 - ???????? ?????????? ??? STM32F303
2013-12-10 - usb ???????? ?? ???????? ????????? ????????? ? ???????.
2013-12-11 - ?????????? DAC
2013-12-13 - ???????????? ADC
2013-12-14 - ? continuous ?????? ???????? ????????? ADC
2013-12-14 - ?????????? ?? ??????? 1.2 mhz adc ? ???????? ?? ???????
2013-12-15 - ????????????? DAC ????? ??????? ? ??????? 1 MHz
2013-12-15 - ????????? ???????? ? ????????? 100 ?? - 100 ???
2013-12-16 - ????????? ADC34
2013-12-19 - ??????? Dual Mode, ???? ?????? ???????? Circular ?????
2013-12-19 - ?????? ????????? ???????? DAC ? Dual Mode ? ??????????? ???????.
2013-12-25 - ?????????? ?????????? ????? ??? ????? ??????? ????????? - ?????? ???????????? ??????????????????, ????????? ????????????? ???????? - ?????????? ?????????????? ??????????? ?? +2.5V
2013-12-30 - ????? ???, ??? ????? ???????? SPI
2014-01-01 - ?????????? ????????????? ???????? - ?????? ?????? ? json ??????
2014-01-02 - ?????????????? ????? ????????????? ???????? ? ?????? ?? ? json
2014-01-06 - ?????? volatile ??? release ?????? - ???????? ???????? ?????? ????????? min, max, mid
2014-01-07 - ??????, ??????? ????? ???????? ??????? sin, cos ???????
2014-01-08 - ?????-????? ???????? ?????????? sin/cos - ??????? ?????????? ??? ? ????????? ???????? ???????? ? ?? ?????, ????? ??? ????????
2014-01-08 - ???????? ?????????? sin/cos ?? ?????? ???????? float
2014-01-11 - ???????? ? DAC ???, ????? nsample ???? ?????? ?????? 4 - ??????? ?????? ????????, ??-?? ??????? ??? ???????? ?????????? USB ??????? ????????? ????? ?? ????????
2014-01-12 - ??????????? ??????? ??????? ??????????? ?? ??????? - ????????? ?????????????? ????? ????????? ? ????????? DAC ???????, ????? ?? ???????? ? ?????????? ???????
2014-01-12 - x10 ?????????? ??? ???????? ?? ???????
2014-01-15 C2 100 p -> 33 p R30 100 K -> 56 K - ????????????? ?????????????? ?????? ????????
2014-02-02 - ????? ???????? 3 demo
2014-02-02 - 3demo ??? ???? ????? ???????? ?????? ? ????????
2014-02-02 - ???????? ?????????? SPI2
2014-02-03 - ?????? ???????? ? ??????????? ? ??????? LPS331AP
2014-02-05 - ?????? ?????? ?????????? ????? - ?????? Hi Lo WaterMark
2014-02-05 - ?????????? SPI 8 bit ?? SPI 16 bit - ????????? ???????? ???????? ????? - LcdStr, LcdChr ????????? char ??????
2014-02-08 - ?? ???????? ????? ???????? ?????? ??? Nokia 5110, ?????????? ??? ???????????? ???????, ?????????? ????????? ?????? - ?? ?????????? ????? ???????? ????????? 3.3 nF ???????????, ??? ?????????? ??????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
2014-02-08 - ????????? ???????????? ??????????? ??????? ??? ADC ?? ???????? ????? ?????
2014-02-08 - ?????????? ???????? ???????? - ???????? RC ??????? ????? ?????? ? ?????? ???????? ???????? - ???????? ????????????? ?????????, ????? ???? ?? ??? ????????? ???????
2014-02-11 - ?????????? quadrature encoder
2014-02-12 - ??????????? ????? ???? ????, ????? ?????????? ? 49 ?? ??????
2014-02-13 - ????? ?????? GND ? GNDA - ???????? ????????? VBAT ??????????
2014-02-13 - Vbat ???? ?????????? ? ???????, ? ?? ? ?????
2014-02-16 - ?????? ?????????? SPI1
2014-02-16 - ????????? ???????? HARDWARE SPI1
2014-02-23 - ??????? ?????. - PC6 USB_ON ?????????? - PB10 AN_SW ??????????
2014-03-10 - ??????? ?????????? ????? main.py
2014-03-22 - ????? ??????? ??????? ????????? ??????? ??? DAC
2014-03-26 - ????????? ???????????? ???????? ? ??????????? ?? ??????? (?????? x32 ?? ?????????)
2014-03-29 ?????? ??? IV ??????????
2014-03-29 - ?????? open/short ??????????
2014-04-05 - ????? ??????? ????????????? LC - serial/parallel ??? R
2014-04-11 - ????????? ???????? GainCorrector
2014-04-13 - calculateJson ?????????? ????? ??????????? ?????????????
2014-04-19 - predefinedResistorIdx ??? startGainAuto
2014-04-25 - ?????????? Corrector2x ? ??????
2014-04-25 - open ?????????????
2014-04-26 - short corrector
2014-04-26 - struct CoeffCorrector
2014-04-26 - ?????? ?????????????? ????????????? ?? flash
2014-04-26 - automatic set low pass
2014-04-28 - ??????? dev.reset() ???????? ?????? ?????? ? usb ??????? ??????? ? ??????? ?????!
2014-05-01 - ??????????? LC - SER/PAR ????? ?????????
2014-05-01 - ? continuous mode ???? ?? ?????? ?????????? ????????, ?? ????????????? ?????? ?????????
2014-05-09 - quadrature encoder code
2014-05-10 - TIM7 50 ms interrupt to button up/down check
2014-05-11 - menu frequency ser/par
2014-05-11 - ?????????? ???????? ?????????? ????? ???? - ???????? ??? ???????????? Rim ??? L/C
2014-05-11 - ???? ???????????, ??-?? ???? ?? ?????????????? 200-300 ?? ???? ??????? Rim ??? ???? ??-?? ??????? ??????? ????????? ?????????!
2014-05-19 - PE1 - light control pin
2014-05-20 - ????????? ???????? ??? ??????????? USB
2014-05-28 - ????? ??????? GainCorrector, ?????? ?? ????? ???????
2014-06-01 - ????? ??????? ??????????, ??? ????????????? gain_corrector
2014-06-01 - ??????????? ? ????????????? ???????? ????????? - ?????? ?????? ??? OPEN ???????????
2014-06-04 - ????????????? ????????? ?????? 100 ???. - ????????? ????????? open ???? ????? ??? ??????? ???????? ? ??????? ?????????? ?? ????
2014-06-06 - ?????? ????????? corrector.c - ????????? ???????? ???????????? ???????? ?? ??????????? ?????????? - ?????? ?????????? ????????? ??? ?????? corrector2x
2014-06-07 - ????????? ?????? ??????????? gain ???????? (????????? ?? 1 ????????)
2014-06-07 - ?????????? open ????????????? ? ??????
2014-06-07 - ?????? ?? flash - ??? ????????? ???????? ??? ADC, ???????? ???????? ???? ? ????????
2014-06-08 - ????????????? 1 ?? - ??????????? ???????? ?? ??????? ???????? ? ?????? - 250 ??? ??????? ? ??????
2014-06-09 - ???? ?????????? ?????????? code - ??????? ????????? ? ????????? ???????
2014-06-09 ????????????? voltage.c -> usb_commands.c
2014-06-09 - add pdf circuit
2014-06-10 - infos
2014-06-10 - update source.mk
2014-06-14 - ?????? ?? ?????????? load-load ??????????, ???????? ?? ?? open-load, ??? ?????? ??????? ???.
2014-06-14 - 187.5 ??? ???????
2014-06-14 - ???????? ???????? - ?????? ???? printGradus = carg(Zx)...
2014-07-03 - d????? ???????????????? ?????????
2014-07-07 - ??????? ???????? ??? ???????????? 3 ?????? ??? ?????????? ?????? ????????
2014-07-08 - ??????? ??????? ?????? A ? B
2014-07-25 - ?????? ???????? USB descriptions
2014-07-26 - MessageBox
2014-07-26 - ClearCorrector - ???? ?????????????? ???????????? ?? ???????, ?? ??????? ???????????? ????????
2014-07-30 - onboard short correction
2014-07-30 - ?????????? ???????? ?? 0 ?? 100 ??? - ???????? ????????
2014-07-31 - open calibration
2014-08-01 - ??????? flash ????? ??????? ?????????????? ????????????? - ????? ???? CLEAR - ??????? ????????????? ?????? ??? ??????? ???????
2014-08-15 - ?????? ? ili9341 ???????? - ????????? ?????? ?????? ? pcd8544 ???????? ? ????????? ?????
2014-09-24 - AD9958 first code
2014-11-19 - ??? ????????????? STD ????????? ???? ???????????????? ??? ????, ????? ????? ???? "??????????? ??????"
2015-06-19 Migrating wiki contents from Google Code
2015-09-09 Working commit
2015-09-09 Ignore Keil message float _ComplexKB: Unexpected type: 6 (check out Browse Information in project options)
